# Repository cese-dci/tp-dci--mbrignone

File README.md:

## Trabajo final Diseño de Circuitos Impresos

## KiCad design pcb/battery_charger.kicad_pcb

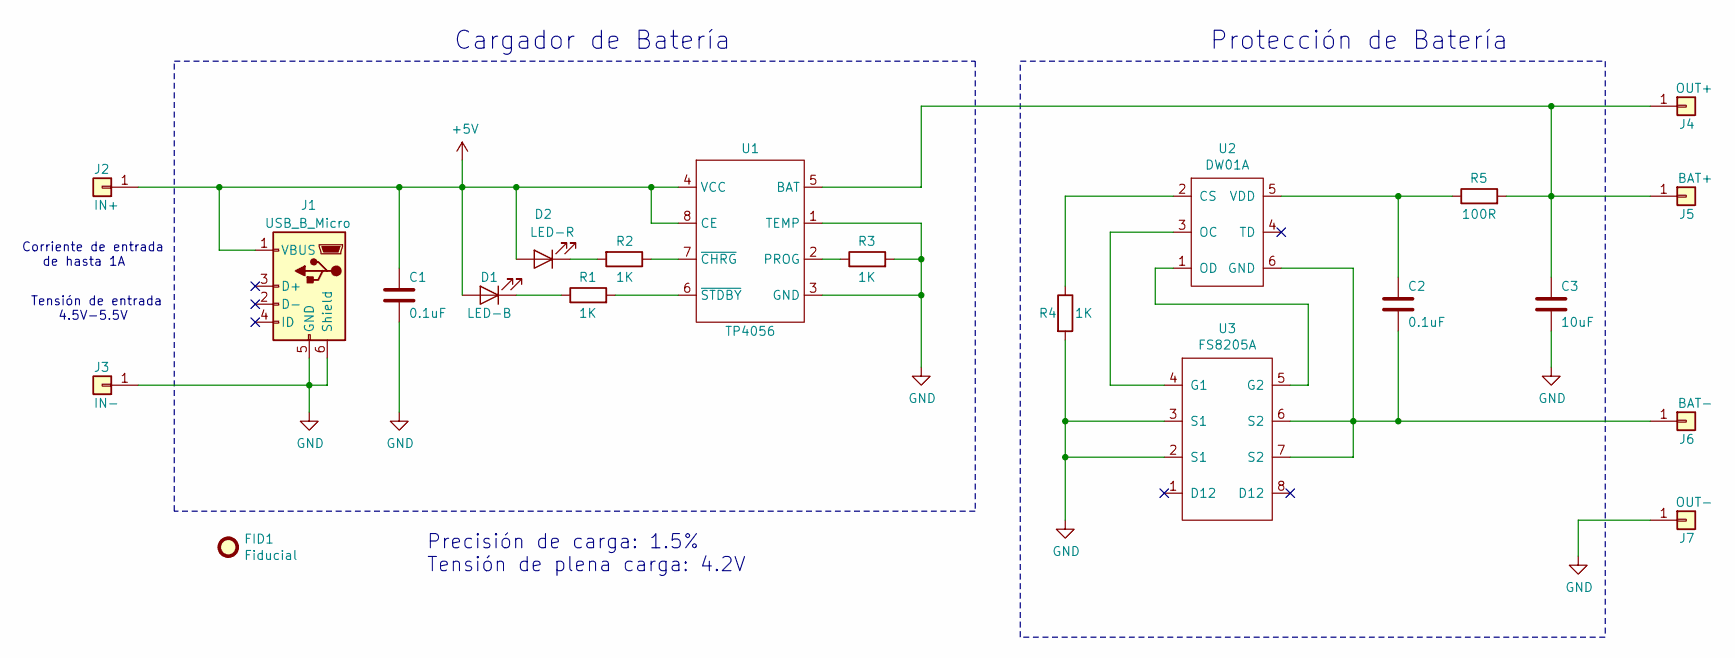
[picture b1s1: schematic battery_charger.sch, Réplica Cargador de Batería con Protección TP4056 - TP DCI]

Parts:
C1, C2: 0.1uF; C_0805_2012Metric; Digikey # 399-1169-2-ND
C3: 10uF; C_1206_3216Metric; Digikey # 399-8153-2-ND
D1: LED-B; LED_0805_2012Metric; Digikey # 160-1645-2-ND
D2: LED-R; LED_0805_2012Metric; Digikey # 160-1427-2-ND
FID1: Fiducial; Fiducial_0.5mm_Mask1mm
J1: USB_B_Micro; USB_Micro-B_GCT_USB3076-30-A; Digikey # 609-4616-1-ND
J2: IN+; SolderWirePad_1x01_Drill0.8mm
J3: IN-; SolderWirePad_1x01_Drill0.8mm
J4: OUT+; SolderWirePad_1x01_Drill0.8mm
J5: BAT+; SolderWirePad_1x01_Drill0.8mm
J6: BAT-; SolderWirePad_1x01_Drill0.8mm
J7: OUT-; SolderWirePad_1x01_Drill0.8mm
R1, R2, R3, R4: 1K; R_0805_2012Metric; Digikey # RPC0805JT1K00TR-ND
R5: 100R; R_0805_2012Metric; Digikey # 2019-RK73B2ATTD101JTR-ND
U1: TP4056; SOP-8_3.76x4.96mm_P1.27mm
U2: DW01A; SOT-23-6
U3: FS8205A; TSSOP-8_4.4x3mm_P0.65mm

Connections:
+5V: C1.1, D1.2 (A), D2.2 (A), J1.1 (VBUS), J2.1, U1.4 (VCC), U1.8 (CE)
GND: C1.2, C3.2, J1.5 (GND), J1.6 (Shield), J3.1, J7.1, R3.2, R4.2, U1.1 (TEMP), U1.3 (GND), U3.2 (S1), U3.3 (S1)
unnamed: C2.1, R5.1, U2.5 (VDD)
unnamed: C2.2, J6.1, U2.6 (GND), U3.6 (S2), U3.7 (S2)
unnamed: C3.1, J4.1, J5.1, R5.2, U1.5 (BAT)
unnamed: D1.1 (K), R1.1
unnamed: D2.1 (K), R2.2
unnamed: R1.2, U1.6 (~STDBY)
unnamed: R2.1, U1.7 (~CHRG)
unnamed: R3.1, U1.2 (PROG)
unnamed: R4.1, U2.2 (CS)
unnamed: U2.1 (OD), U3.5 (G2)
unnamed: U2.3 (OC), U3.4 (G1)

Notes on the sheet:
Cargador de Batería
Protección de Batería
Corriente de entrada de hasta 1A
Tensión de entrada 4.5V-5.5V
Precisión de carga: 1.5% Tensión de plena carga: 4.2V

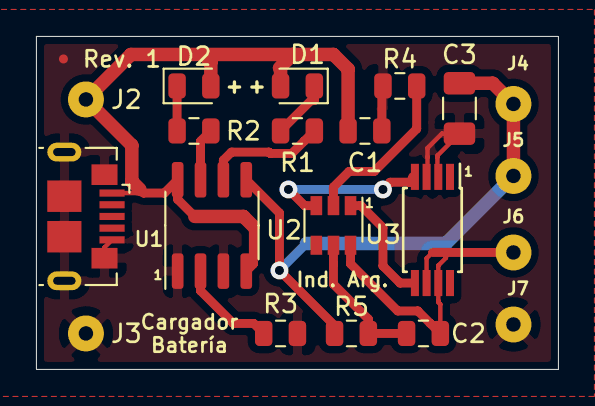
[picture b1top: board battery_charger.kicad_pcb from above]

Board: 2 copper layers, 29.0 x 18.5 mm, 21 parts (0 on the bottom side), 13 nets.

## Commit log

2019-09-22 add initial readme
2019-09-25 Se agrega explicacion del circuito a realizar
2019-09-25 Se agrega proyecto de Kicad con esquematico terminado
2019-09-28 Cambiar pines a passive en libreria de simbolos propia
2019-09-28 Se agregan datasheets de componentes
2019-09-28 Se agregan fotos del modulo
2019-10-06 Correcciones al esquematico de acuerdo a revision de compañero + comienzo de PCB layout
2019-10-06 Primera version del PCB layout
2019-10-06 Se optimiza el area ocupada por el pcb
2019-10-06 Se agrega relleno de cobre
2019-10-06 Se elimina via innecesaria
2019-10-06 Se acomodan conectores y se cambian referencias en pcb
2019-10-06 Se agregan modelos 3D
2019-10-06 Se agrega rotulo y cotas al pcb
2019-10-06 Correcciones generales al pcb
2019-10-19 Se agrega esquematica original en info
2019-10-19 Correcciones a esquematico
2019-10-20 Importantes mejoras en el PCB
2019-10-20 Se agregan referencias del fabricante
2019-10-20 Se cambian vias de 0.8mm por vias de 1mm
2019-10-27 Se realizan correcciones al PCB
2019-11-02 Se hacen correcciones finales de acuerdo a revision del docente
